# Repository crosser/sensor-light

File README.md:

## LED strip light controller ##

The project is to drive night lighting of a staircase using PIR
motion sensors (two: for the top and bottom of the staircase).
Ambient light sensor to only turn the LED chain when it is dark.
Driven by MSP430 MCU, light power controlled via PWM + MOSFET.

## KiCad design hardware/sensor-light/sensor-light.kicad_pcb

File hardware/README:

Using this suggestion from electronics stackexchange:

https://electronics.stackexchange.com/questions/67775/driving-led-strip-from-microcontroller

MOSFET datasheet:

https://www.infineon.com/dgdl/irlml2502.pdf?fileId=5546d462533600a401535667f44d2602

MCU Power supply datasheet:

https://www.sparkfun.com/datasheets/Components/LD1117V33.pdf

Possible alternative MOSFET:

https://assets.nexperia.com/documents/data-sheet/PMV20XNE.pdf

Other parts:
Power regulator for MCU: TLV76033DBZT (TI, SOT-23-3, 100mA)
Schottky Diode power in: 757-1SS404H3F (Toschiba, SOT-323-3, 300mA, 0.38V drop)
			 PMEG6020ER (Nexperia, SOD123W, 2A, .5V drop)

Resistors for LEDs:
Red: 470
Green: 390 (270)

LEDs: TLLR4400, TLLG4400 Vishay Semiconductors
Vf=1.9V
If=2mA

Connector: AKZ692/4
https://www.ptr.eu/no_cache/en/produkte/produkt-pdf-generator/?cat_id=355

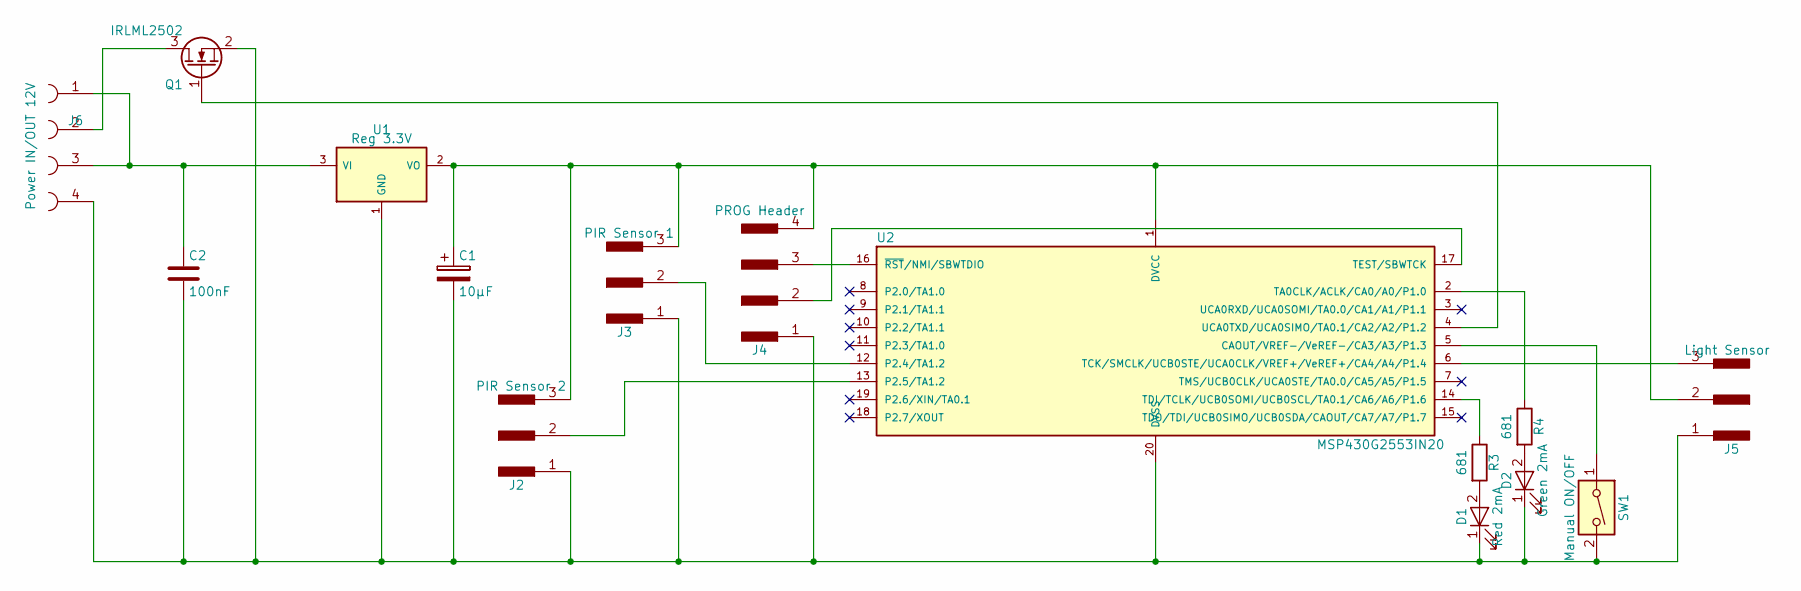
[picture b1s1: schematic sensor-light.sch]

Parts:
C1: 10μF; CP_Radial_D5.0mm_P2.50mm
C2: 100nF; C_Rect_L7.0mm_W2.5mm_P5.00mm
D1: Red 2mA; LED_D3.0mm
D2: Green 2mA; LED_D3.0mm
J2: PIR Sensor 2; Socket_Strip_Straight_1x03_Pitch2.54mm
J3: PIR Sensor 1; Socket_Strip_Straight_1x03_Pitch2.54mm
J4: PROG Header; Socket_Strip_Straight_1x04_Pitch2.54mm
J5: Light Sensor; Socket_Strip_Straight_1x03_Pitch2.54mm
J6: Power IN/OUT 12V; AKZ692_4
Q1: IRLML2502; SOT-23_Handsoldering
R3, R4: 681; R_Axial_DIN0411_L9.9mm_D3.6mm_P12.70mm_Horizontal
SW1: Manual ON/OFF; SW_PUSH_6mm_h5mm
U1: Reg 3.3V; SOT-223
U2: MSP430G2553IN20; DIP-20_W7.62mm_Socket

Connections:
unnamed: C1.1, J2.3, J3.3, J4.4, J5.2, U1.2 (VO), U2.1 (DVCC)
unnamed: C1.2, C2.2, D1.1 (K), D2.1 (K), J2.1, J3.1, J4.1, J5.1, J6.4, Q1.2 (S), SW1.2, U1.1 (GND), U2.20 (DVSS)
unnamed: C2.1, J6.1, J6.3, U1.3 (VI)
unnamed: D1.2 (A), R3.2
unnamed: D2.2 (A), R4.2
unnamed: J2.2, U2.13 (P2.5/TA1.2)
unnamed: J3.2, U2.12 (P2.4/TA1.2)
unnamed: J4.2, U2.17 (TEST/SBWTCK)
unnamed: J4.3, U2.16 (~RST~/NMI/SBWTDIO)
unnamed: J5.3, U2.6 (TCK/SMCLK/UCB0STE/UCA0CLK/VREF+/VeREF+/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)
unnamed: J6.2, Q1.3 (D)
unnamed: Q1.1 (G), U2.4 (UCA0TXD/UCA0SIMO/TA0.1/CA2/A2/P1.2)
unnamed: R3.1, U2.14 (TDI/TCLK/UCB0SOMI/UCB0SCL/TA0.1/CA6/A6/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)
unnamed: R4.1, U2.2 (TA0CLK/ACLK/CA0/A0/P1.0)
unnamed: SW1.1, U2.5 (CAOUT/VREF-/VeREF-/CA3/A3/P1.3)

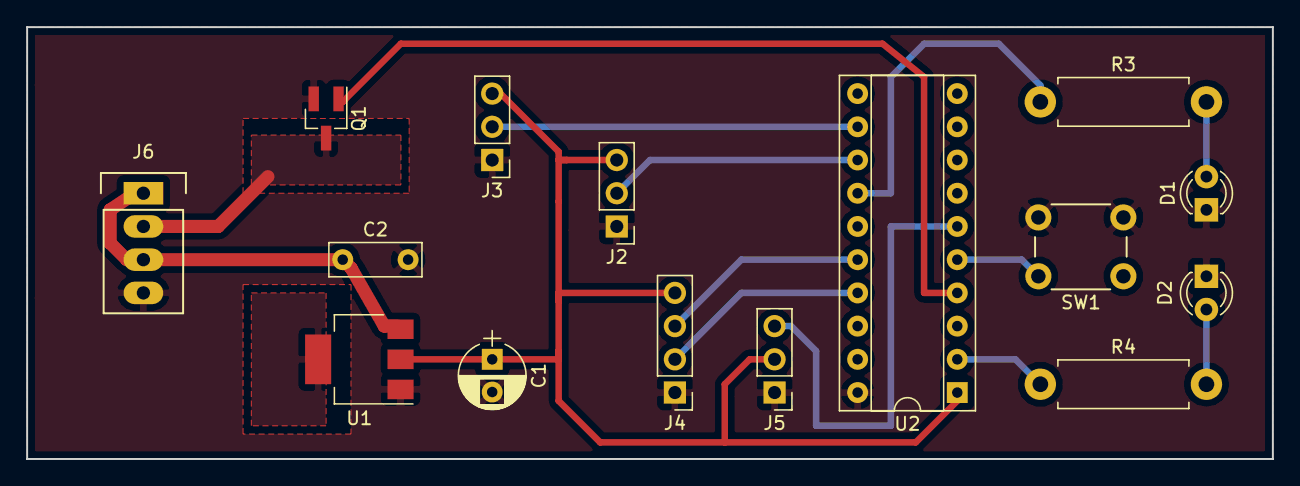
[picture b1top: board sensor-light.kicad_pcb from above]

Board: 2 copper layers, 95.2 x 33.0 mm, 15 parts (0 on the bottom side), 15 nets.

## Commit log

2017-12-10 Initial msp430 program
2017-12-10 Automated reformat
2017-12-11 fix typos/loose defines
2017-12-11 formatting
2017-12-11 Initial Makefile
2017-12-12 tune up Makefile
2017-12-13 add PINOUT file
2017-12-13 use model-dependent GPIO bits
2017-12-13 parametrize button interrupts per model
2017-12-13 adapt to msp430g2
2017-12-13 adjust makefile for G2
2017-12-13 make PWM work on G2
2017-12-13 fix loading in Makefile
2017-12-13 use zero duty cycle for zero
2017-12-14 add initial schematics
2017-12-14 add some READMEs
2017-12-14 fix README formatting
2017-12-29 add picture of the MOSFET
2018-01-01 Make some electrical schematic with KiCad
2018-01-01 Fix typos in the README
2018-01-01 change pin flags to make ERC happy
2018-01-01 change lables on the schematic
2018-01-01 remove experimental schematics
2018-01-01 remove extra line on the schematics
2018-01-01 first attempt to assign footprints and make a pcb
2018-01-01 forgot the pcb file
2018-01-01 mention alternative MOSFET model
2018-01-02 make LED indication more meaningful
2018-01-02 streamline logic, adjust ambient light value
2018-01-02 make PWM duty cycle change more smoothly
2018-01-03 add resistors to the indicator LEDs
2018-01-03 add notes about possible parts for the project
2018-01-05 streamline logic, change light threshold
2018-01-06 adjust time to wait and light threshold
2018-02-10 attempt to place components on the PCB
2018-02-13 some attempt of pcb routing
2018-02-16 LED resistor values
2018-02-19 correct MOSFET pinout
2018-02-19 Attempt at laying out the board
2018-02-20 try adust layout
2018-02-20 save unsaved
2018-02-20 they are called geRber, right?
2018-02-20 add capacitor to the regulator input
2018-02-21 layout adjustments
2018-02-21 some fiddling with thermal releif areas
2018-02-21 rebuild picture of the schematics
2018-02-21 redraw board, with correct releif areas
2018-02-22 minor adjustment in traces and labels
2018-02-23 play with BOM creation
2018-02-23 Change the power connector type
    because I could not order AK300 :-\
2018-02-26 export missing gerber files
2018-03-19 disable pull up/down - PIR signal too weak
2018-03-24 Add picture of the finished device
2018-03-24 Replace final picture
